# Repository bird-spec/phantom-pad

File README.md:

# phantom pad

this is the pcb for my phantom macropad. it's a little keyboard that doubles as a controller for my drone. twelve mechanical keys in a 3x4 matrix plus two rotary encoders, all running off a seeed xiao

the whole point is one board that's both a keyboard and a flight controller. rotate the encoders for throttle and yaw, and the four keys around each one act like a d-pad for direction. slide the top section off and it's just a normal macropad again

it's a two layer board. i wired the switches in a matrix so twelve keys only need seven pins instead of twelve, which left enough pins free for the two encoders. every switch has a diode so pressing three keys at once doesn't register a fourth one that isn't pressed

this was my first pcb ever. i learned kicad from nothing to make it. the hardest part was the routing, and figuring out that a matrix needs the rows and columns to actually reach the microcontroller, which sounds obvious but isn't when you're staring at a wall of green lines

made with the seeed xiao, cherry mx footprints, and alps ec11 encoders. firmware runs on qmk

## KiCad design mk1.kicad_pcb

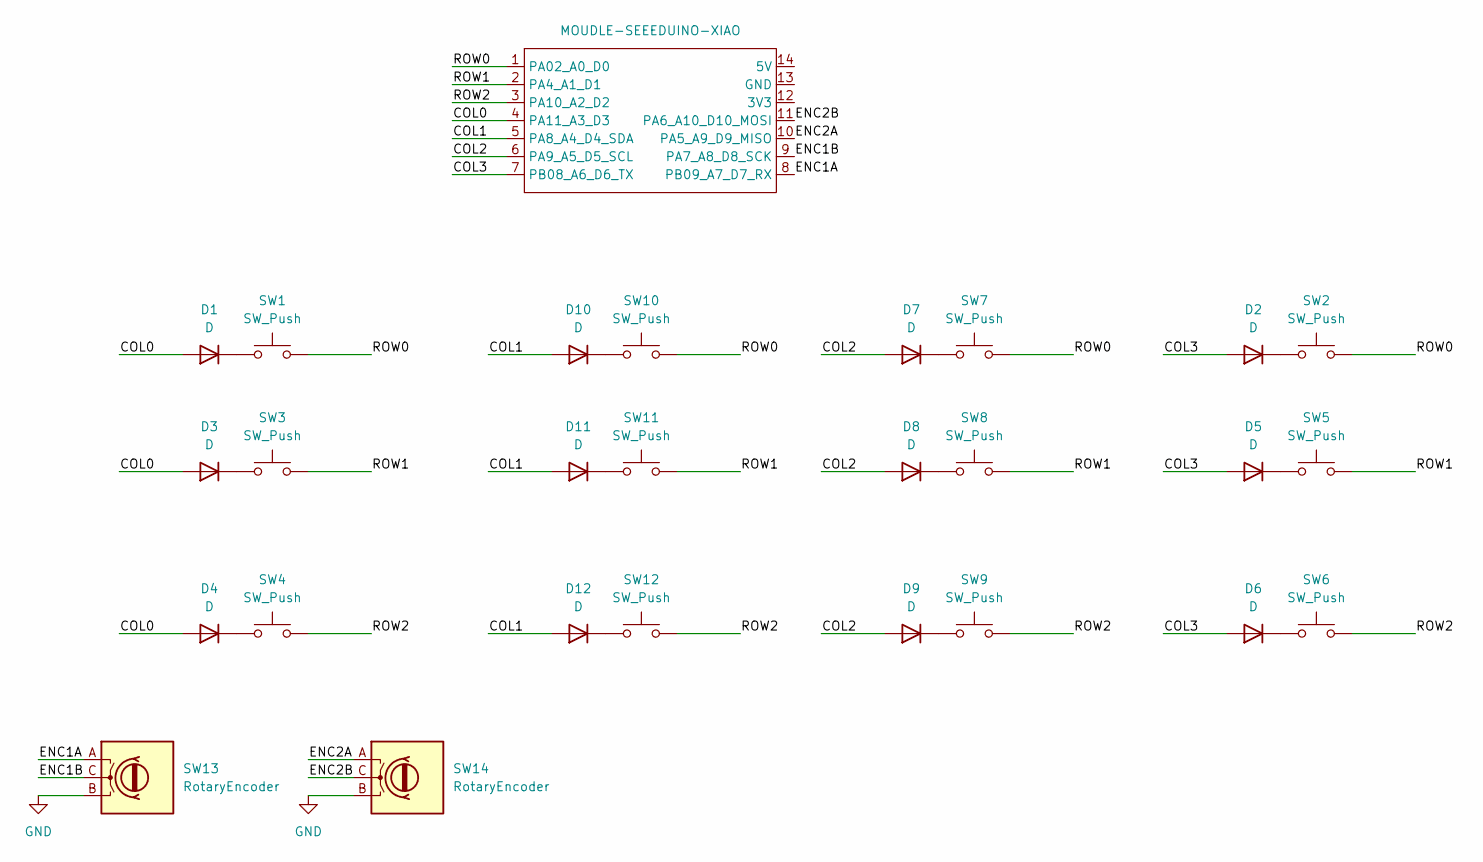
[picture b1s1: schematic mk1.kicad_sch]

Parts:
D1, D2, D3, D4, D5, D6, D7, D8, D9, D10, D11, D12: D; D_SOD-123
SW1, SW2, SW3, SW4, SW5, SW6, SW7, SW8, SW9, SW10, SW11, SW12: SW_Push; SW_Cherry_MX_1.00u_PCB
SW13, SW14: RotaryEncoder; RotaryEncoder_Alps_EC11E-Switch_Vertical_H20mm
U1: MOUDLE-SEEEDUINO-XIAO; XIAO-Generic-Hybrid-14P-2.54-21X17.8MM

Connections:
/COL0: D1.2 (A), D3.2 (A), D4.2 (A), U1.4 (PA11_A3_D3)
/COL1: D10.2 (A), D11.2 (A), D12.2 (A), U1.5 (PA8_A4_D4_SDA)
/COL2: D7.2 (A), D8.2 (A), D9.2 (A), U1.6 (PA9_A5_D5_SCL)
/COL3: D2.2 (A), D5.2 (A), D6.2 (A), U1.7 (PB08_A6_D6_TX)
/ENC1A: SW13.A, U1.8 (PB09_A7_D7_RX)
/ENC1B: SW13.C, U1.9 (PA7_A8_D8_SCK)
/ENC2A: SW14.A, U1.10 (PA5_A9_D9_MISO)
/ENC2B: SW14.C, U1.11 (PA6_A10_D10_MOSI)
/ROW0: SW1.2, SW2.2, SW7.2, SW10.2, U1.1 (PA02_A0_D0)
/ROW1: SW3.2, SW5.2, SW8.2, SW11.2, U1.2 (PA4_A1_D1)
/ROW2: SW4.2, SW6.2, SW9.2, SW12.2, U1.3 (PA10_A2_D2)
GND: SW13.B, SW14.B
unnamed: D1.1 (K), SW1.1
unnamed: D2.1 (K), SW2.1
unnamed: D3.1 (K), SW3.1
unnamed: D4.1 (K), SW4.1
unnamed: D5.1 (K), SW5.1
unnamed: D6.1 (K), SW6.1
unnamed: D7.1 (K), SW7.1
unnamed: D8.1 (K), SW8.1
unnamed: D9.1 (K), SW9.1
unnamed: D10.1 (K), SW10.1
unnamed: D11.1 (K), SW11.1
unnamed: D12.1 (K), SW12.1

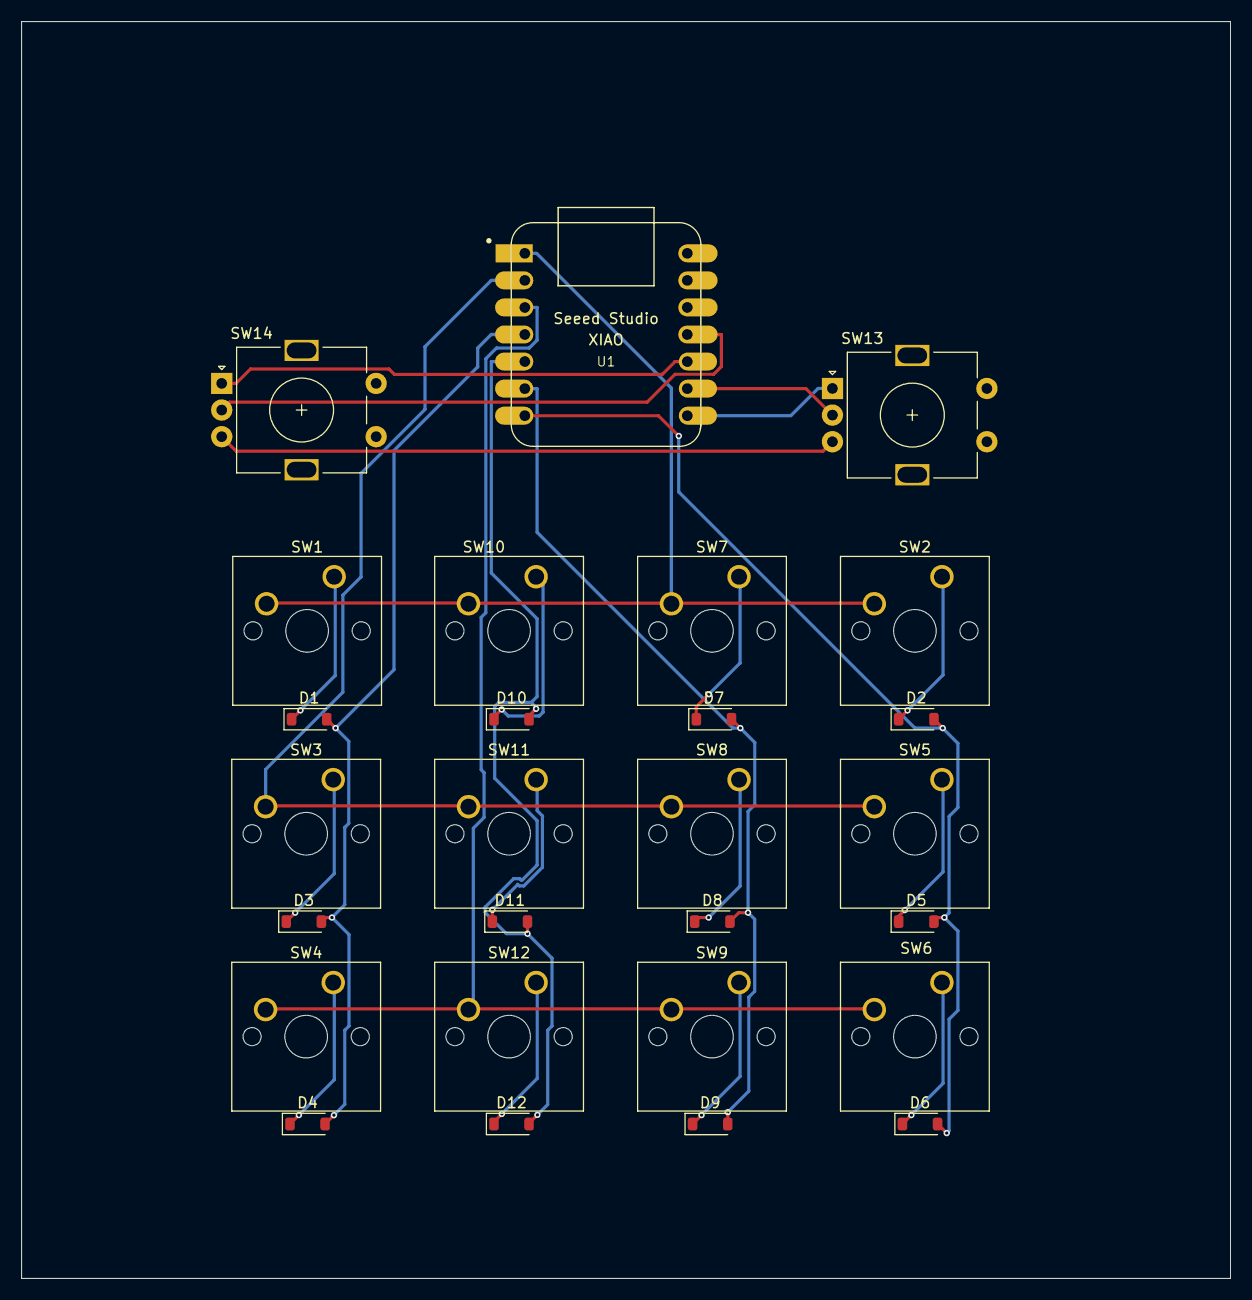
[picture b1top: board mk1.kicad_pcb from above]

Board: 2 copper layers, 113.5 x 118.0 mm, 27 parts (0 on the bottom side), 24 nets.
